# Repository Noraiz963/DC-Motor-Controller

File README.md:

# PWM DC Motor Speed Controller (555 Timer Based)

A simple, low-cost DC motor speed controller built around the classic NE555P timer IC. The 555 runs in astable mode with an asymmetric charge/discharge network to generate a variable duty-cycle PWM signal, which drives a TIP122 Darlington transistor to switch the motor. A single potentiometer gives smooth control over motor speed.

## Schematic

## PCB Layout

## 3D Render

## How It Works

The circuit is built around four functional blocks:

### 1. Power Input & Filtering
Power enters through a 3.5mm terminal (J2). A 1000µF capacitor (C1) smooths the supply rail so switching transients from the motor don't disturb the 555's timing. A 2.2k resistor (R1) drives an LED (D4) as a power-on indicator.

### 2. Timing / PWM Generation Network
The NE555P (U1) is configured as an astable oscillator. Instead of a single resistor, the charge and discharge paths are separated using two steering diodes (D1, D2) around a 100k potentiometer (RV1). This lets the charge time and discharge time be adjusted independently, producing a duty cycle that can be swept across a wide range — from mostly off to mostly on — rather than being stuck above 50% like a standard 555 astable. R2 (1k) limits current into the 555's internal discharge transistor. C2 (100nF) is the timing capacitor. C3 (100nF) bypasses the CONTROL pin per the 555 datasheet recommendation, keeping the internal reference stable.

### 3. Output / Motor Drive Stage
The 555's OUT pin drives the base of Q1 (TIP122) through a 1k base resistor (R3). The TIP122 is a Darlington transistor capable of switching several amps, acting as the actual power switch for the motor while the 555 only supplies the low-current control signal. As RV1 is adjusted, the PWM duty cycle changes, which changes the average voltage delivered to the motor — and therefore its speed.

### 4. Flyback Protection
Because a DC motor is an inductive load, switching it off abruptly causes a voltage spike as the motor's magnetic field collapses. A flyback diode (D3, 1N4007) is placed across the motor output to safely clamp this spike and protect Q1 from damage.

### Signal Flow
```
J2 (DC in) → C1 filter → 555 astable (RV1 sets duty cycle)
           → 555 OUT → R3 → Q1 (TIP122) base
           → Q1 switches motor at J1, PWM-style
           → D3 clamps inductive kickback on every switch-off
```

## Bill of Materials

| Ref | Value | Description |
|-----|-------|-------------|
| U1 | NE555P | Timer IC, astable PWM generator |
| Q1 | TIP122 | NPN Darlington transistor, motor switch |
| RV1 | 100k | Potentiometer, speed/duty-cycle control |
| R1 | 2.2k | LED current limiting resistor |
| R2 | 1k | 555 discharge current limiting resistor |
| R3 | 1k | Q1 base resistor |
| C1 | 1000µF | Input filter / bulk capacitor |
| C2 | 100nF | Timing capacitor |
| C3 | 100nF | 555 CONTROL pin bypass capacitor |
| D1, D2 | 1N4007 | Charge/discharge steering diodes |
| D3 | 1N4007 | Flyback protection diode |
| D4 | LED | Power-on indicator |
| J1 | 3.5mm terminal | Motor output |
| J2 | 3.5mm terminal | DC power input |

## Specifications

- **Board size:** A4 sheet design, compact 4-hole mount PCB
- **Input:** DC supply via 3.5mm terminal (voltage rating depends on motor and TIP122 limits)
- **Output:** Switched DC to motor via 3.5mm terminal, protected with flyback diode
- **Control:** Single potentiometer, adjustable PWM duty cycle
- **Design tool:** KiCad 10.0.4

## Usage

1. Connect a DC power supply to J2, matching your motor's voltage requirements.
2. Connect the DC motor to J1.
3. Power on — the LED (D4) will light to confirm the supply is active.
4. Turn RV1 to adjust motor speed from low to high.

## Notes / Possible Improvements

- Add a flyback/snubber network closer to the motor terminals for noisy or high-inductance motors.
- Consider a heatsink for Q1 if driving higher current motors continuously.
- A reverse-polarity protection diode on the input could be added for extra robustness.

## Author

Designed by MAKER.

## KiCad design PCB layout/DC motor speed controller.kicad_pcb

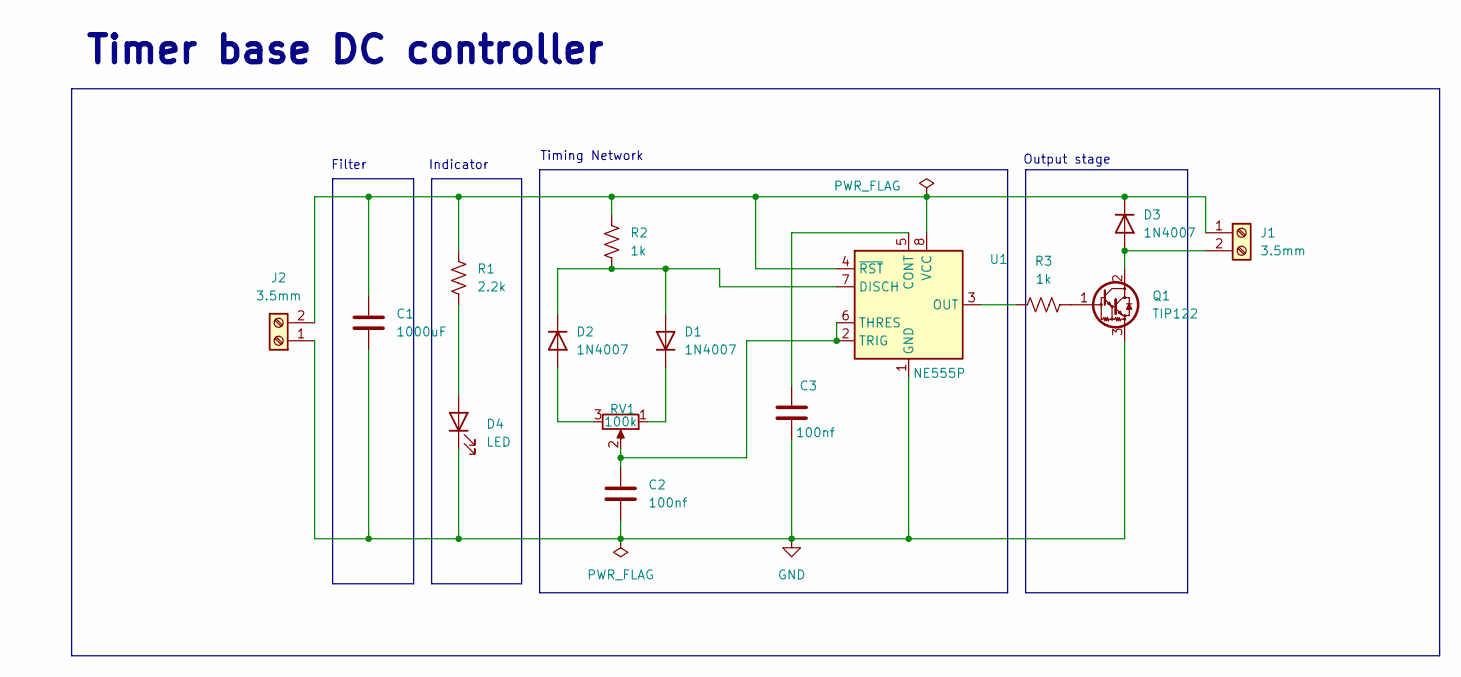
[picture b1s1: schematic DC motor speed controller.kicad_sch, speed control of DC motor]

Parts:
C1: 1000uF; CP_Radial_D10.0mm_P5.00mm_P7.50mm
C2, C3: 100nf; C_Disc_D4.7mm_W2.5mm_P5.00mm
D1, D2, D3: 1N4007; D_DO-41_SOD81_P10.16mm_Horizontal
D4: LED; LED_D5.0mm
J1, J2: 3.5mm; TerminalBlock_MaiXu_MX126-5.0-02P_1x02_P5.00mm
Q1: TIP122; TO-220-3_Vertical
R1: 2.2k; R_Axial_DIN0204_L3.6mm_D1.6mm_P7.62mm_Horizontal
R2, R3: 1k; R_Axial_DIN0204_L3.6mm_D1.6mm_P7.62mm_Horizontal
RV1: 100k; Potentiometer_Alps_RK163_Single_Horizontal
U1: NE555P; DIP-8_W7.62mm

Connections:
GND: C1.2, C2.2, C3.2, D4.1 (K), J2.1, Q1.3 (E), U1.1 (GND)
unnamed: D1.2 (A), D2.1 (K), R2.2, U1.7 (DISCH)
unnamed: D1.1 (K), RV1.1
unnamed: D2.2 (A), RV1.3
unnamed: D3.2 (A), J1.2, Q1.2 (C)
unnamed: C1.1, D3.1 (K), J1.1, J2.2, R1.1, R2.1, U1.4 (~RST), U1.8 (VCC)
unnamed: D4.2 (A), R1.2
unnamed: Q1.1 (B), R3.1
unnamed: C3.1, U1.5 (CONT)
unnamed: R3.2, U1.3 (OUT)
unnamed: C2.1, RV1.2, U1.2 (TRIG), U1.6 (THRES)

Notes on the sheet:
Timing Network
Output stage
Timer base DC controller
Indicator
Filter

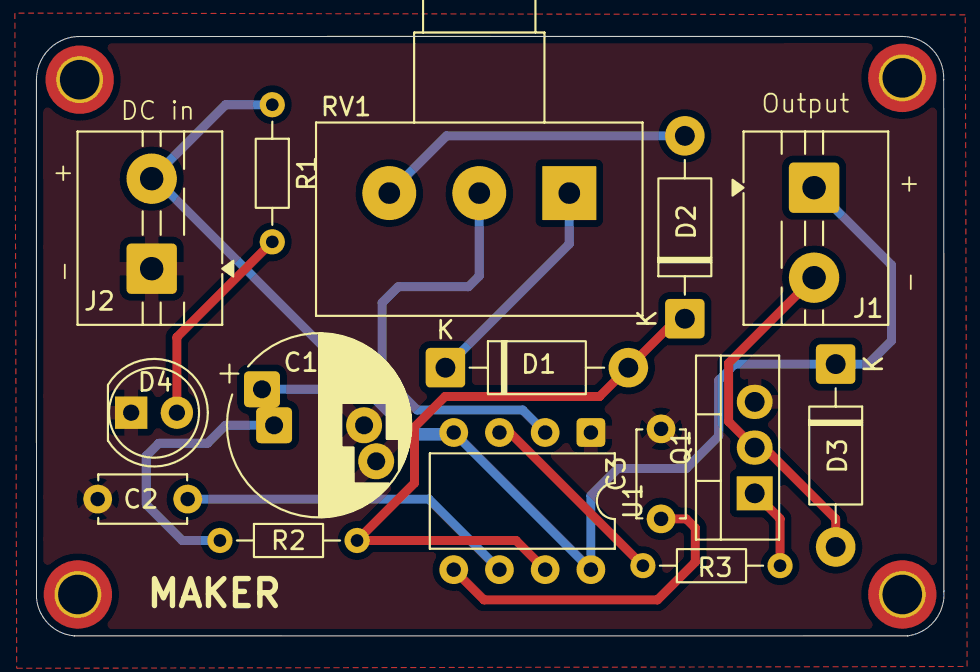
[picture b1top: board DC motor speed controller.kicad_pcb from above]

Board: 2 copper layers, 50.4 x 33.3 mm, 15 parts (0 on the bottom side), 11 nets.
